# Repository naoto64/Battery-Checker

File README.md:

# Battery-Checker
Battery checker that displays the remaining charge of a 1.5V battery in two stages

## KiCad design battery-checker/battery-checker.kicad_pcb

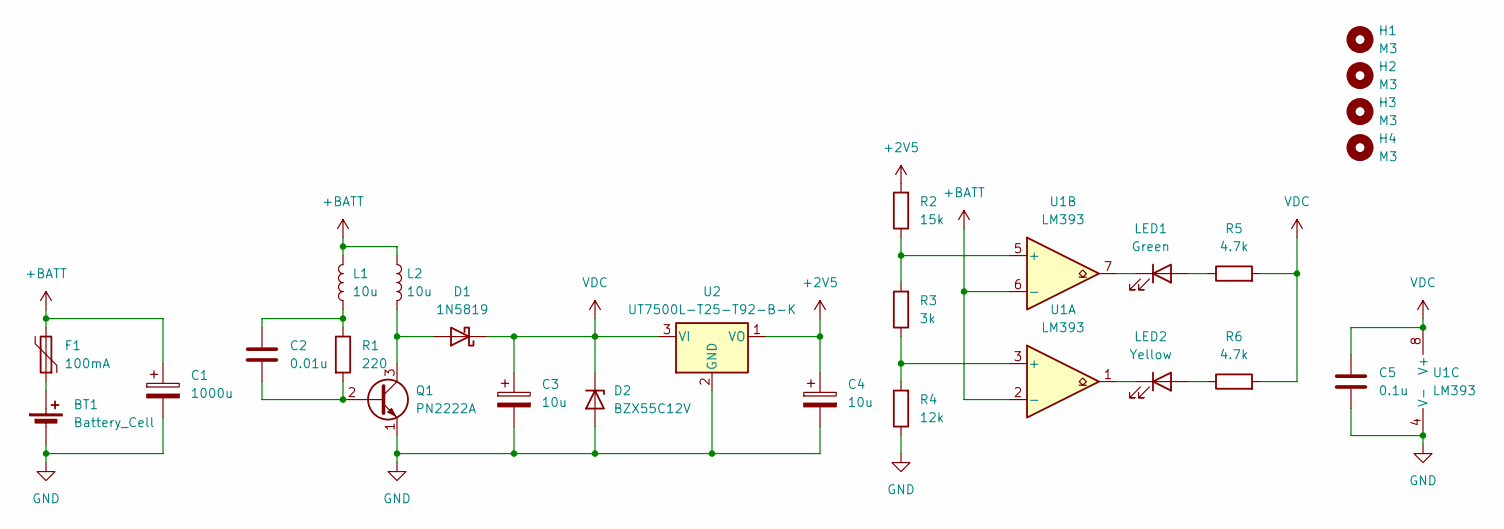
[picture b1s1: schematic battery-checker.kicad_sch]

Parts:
BT1: Battery_Cell; SolderWire-0.1sqmm_1x02_P3.6mm_D0.4mm_OD1mm_Relief
C1: 1000u; CP_Radial_D10.0mm_P5.00mm
C2: 0.01u; C_Disc_D4.3mm_W1.9mm_P5.00mm
C3, C4: 10u; CP_Radial_D5.0mm_P2.00mm
C5: 0.1u; C_Disc_D4.3mm_W1.9mm_P5.00mm
D1: 1N5819; D_DO-41_SOD81_P10.16mm_Horizontal
D2: BZX55C12V; D_DO-35_SOD27_P7.62mm_Horizontal
F1: 100mA; Fuse_Bourns_MF-RG300
H1, H2, H3, H4: M3; MountingHole_3.2mm_M3
L1, L2: 10u; L_Axial_L5.3mm_D2.2mm_P7.62mm_Horizontal_Vishay_IM-1
LED1: Green; LED_D5.0mm
LED2: Yellow; LED_D5.0mm
Q1: PN2222A; TO-92L_Inline_Wide
R1: 220; R_Axial_DIN0207_L6.3mm_D2.5mm_P7.62mm_Horizontal
R2: 15k; R_Axial_DIN0207_L6.3mm_D2.5mm_P7.62mm_Horizontal
R3: 3k; R_Axial_DIN0207_L6.3mm_D2.5mm_P7.62mm_Horizontal
R4: 12k; R_Axial_DIN0207_L6.3mm_D2.5mm_P7.62mm_Horizontal
R5, R6: 4.7k; R_Axial_DIN0207_L6.3mm_D2.5mm_P7.62mm_Horizontal
U1: LM393; DIP-8_W7.62mm_Socket
U2: UT7500L-T25-T92-B-K; TO-92L_Inline_Wide

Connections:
+2V5: C4.1, R2.2, U2.1 (VO)
+BATT: C1.1, F1.2, L1.2, L2.1, U1.2 (-), U1.6 (-)
GND: BT1.2 (-), C1.2, C3.2, C4.2, C5.1, D2.2 (A), Q1.1 (E), R4.1, U1.4 (V-), U2.2 (GND)
unnamed: BT1.1 (+), F1.1
unnamed: C2.1, L1.1, R1.1
unnamed: D1.2 (A), L2.2, Q1.3 (C)
unnamed: LED1.2 (A), R5.1
unnamed: LED1.1 (K), U1.7
unnamed: LED2.2 (A), R6.1
unnamed: LED2.1 (K), U1.1
unnamed: C2.2, Q1.2 (B), R1.2
unnamed: R3.1, R4.2, U1.3 (+)
unnamed: R2.1, R3.2, U1.5 (+)
VDC: C3.1, C5.2, D1.1 (K), D2.1 (K), R5.2, R6.2, U1.8 (V+), U2.3 (VI)

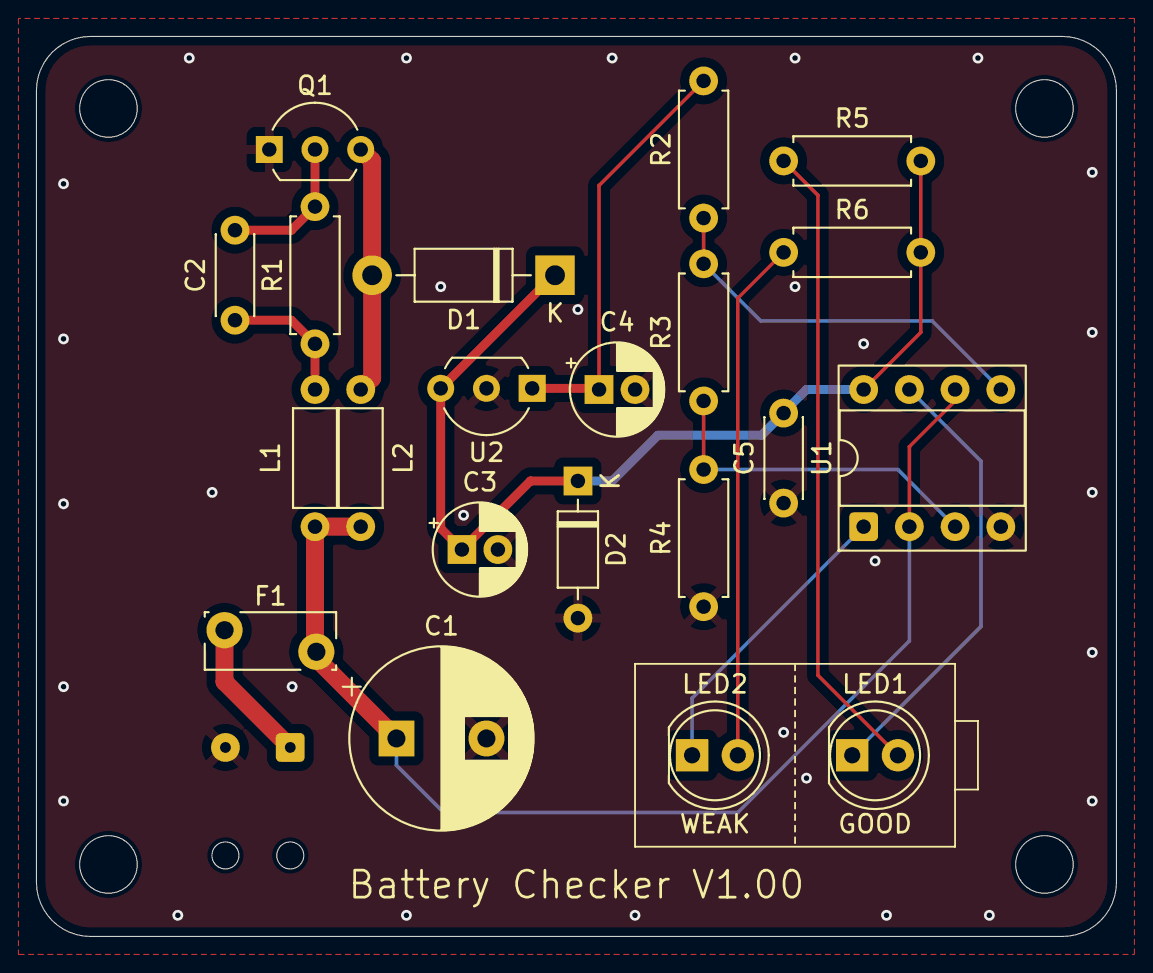
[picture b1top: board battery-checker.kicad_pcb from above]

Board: 2 copper layers, 60.0 x 50.0 mm, 26 parts (1 on the bottom side), 14 nets.

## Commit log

2025-03-01 Rename img/implementation-diagram.jpg to docs/img/implementation-diagram.jpg
2025-03-01 Rename img/schematic.jpg to docs/img/schematic.jpg
